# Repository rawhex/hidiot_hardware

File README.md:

# HIDIOT Hardware

This is the repo for the HIDIOT hardware. It contains the following:

* HIDIOT Schematics and Board definitions for Eagle CAD
* HIDIOT Schematic in PNG format
* This README

The HIDIOT uses the Arduino IDE in either Trinket or Digispark compatible configuration with the appropriate software. Digispark is the preferred framework. Please see [here](https://github.com/digistump/DigistumpArduino) for source code, including the V-USB library used for communication.

## Creating your own HIDIOT

There's a couple of gotchas that you should be aware of depending on what you're using it for and what modifications you want to make. It's probably best to drop an email to pcb@hidiot.com where we can help you make sure your design both works properly and respects our trademarks.

If you're looking to make one for your own personal use, please do fill your boots (but let us know above so we can help).

If you want to create HIDIOTs for an event or a group, we're more than happy for you to do so providing you make your board substantially unique in some way, and you obviously can't use the terms HIDIOT or Raw Hex in your designor name without express written permission. If you want to use these terms, just write to us, and we'll have a chat.

If you're looking to create HIDIOTs commercially, then please make sure that your HIDIOT has a fundamental difference, and of course you can't use terms like HIDIOT or Raw Hex anywhere in your product's design or implementation. You'll also need to be careful about how you use our documentation, which is licenced separately. Talking to us up front will help avoid possible problems later on and we're happy to advise on how to do this correctly.

## Partnering with us

We do provide custom board designs and can provide licences and support for various forms of commercial use. Please contact us at support at rawhex dot com. We'd love to work with you!

## Thanks

There are several people we'd like to thank. All of these people helped, possibly without knowing it. Without these people the HIDIOT would not be possible. If you're not on the list and think you should be, drop us a line.

* Sammy Verity
* Dominic Spill
* Erik Kettenburg
* Saumil Shah
* Dhillon 'L33tdawg' Kannabhiran
* Pete Herzog
* Joe Fitzpatrick
* Don A. Bailey
* cpldcpu
* Jenna Fox
* ihsan Kehribar
* Objective Development Software GmBH
* All of our Kickstarter backers

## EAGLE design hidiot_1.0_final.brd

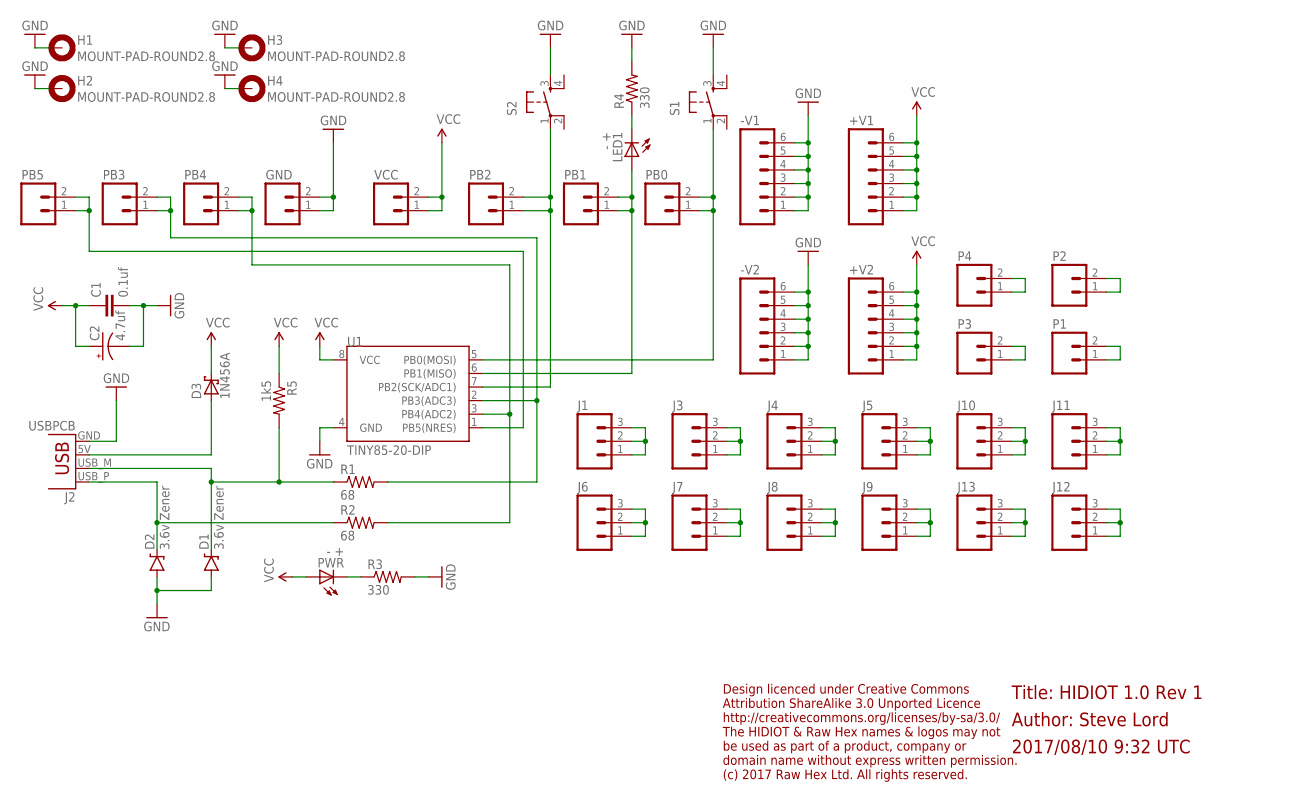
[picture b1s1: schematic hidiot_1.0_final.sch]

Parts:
+V1, +V2: M06SILK_FEMALE_PTH; 1X06
-V1, -V2: M06SILK_FEMALE_PTH; 1X06
C1: 0.1uf; CAP-PTH-SMALL-KIT; MPN K104K15X7RF5TH5
C2: 4.7uf; CPOL-RADIAL-100UF-25V; MPN MCGPR50V475M5X11
D1, D2: 3.6v Zener; DIODE-ZENER; MPN 1N4729A
D3: 1N456A; DIODE_DO35-7; MPN 1N456A
GND: M02PTH; 1X02
H1, H2, H3, H4: MOUNT-PAD-ROUND2.8; 2,8-PAD
J1, J3, J4, J5, J6, J7, J8, J9, J10, J11, J12, J13: M03PTH; 1X03
J2: USBPCB; USB-A-PCB
LED1: - +; LED3MM; MPN HLMP-K150
P1, P2, P3, P4: M02PTH; 1X02
PB0, PB1, PB2, PB3, PB4, PB5: M02PTH; 1X02
PWR: - +; LED3MM; MPN HLMP-K150
R1, R2: 68; AXIAL-0.4; MPN MCF 0.25W 68R
R3, R4: 330; AXIAL-0.4; MPN MCF 0.25W 68R
R5: 1k5; AXIAL-0.4; MPN MCF 1W 1K5
S1, S2: TAC_SWITCHPTH; TACTILE-PTH
U1: TINY85-20-DIP; DIP08; MPN ATTINY85-20PU
VCC: M02PTH; 1X02

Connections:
GND: -V1.1, -V1.2, -V1.3, -V1.4, -V1.5, -V1.6, -V2.1, -V2.2, -V2.3, -V2.4, -V2.5, -V2.6, C1.2, C2.2 (-), D1.P$2 (A), D2.P$2 (A), GND.1, GND.2, H1.B2,8, H2.B2,8, H3.B2,8, H4.B2,8, J2.GND, R3.P$2 (2), R4.P$2 (2), S1.3, S2.3, U1.4 (GND)
unnamed: PB5.1, PB5.2, U1.1 (PB5(NRES))
unnamed: LED1.K (C), R4.P$1 (1)
unnamed: PB2.1, PB2.2, S2.1, U1.7 (PB2(SCK/ADC1))
unnamed: PB3.1, PB3.2, R1.P$2 (2), U1.2 (PB3(ADC3))
unnamed: PB4.1, PB4.2, R2.P$2 (2), U1.3 (PB4(ADC2))
unnamed: PB0.1, PB0.2, S1.1, U1.5 (PB0(MOSI))
unnamed: D2.P$1 (C), J2.USB_P (D+), R2.P$1 (1)
unnamed: D1.P$1 (C), J2.USB_M (D-), R1.P$1 (1), R5.P$2 (2)
unnamed: D3.A (C), J2.5V (VBUS)
unnamed: LED1.A, PB1.1, PB1.2, U1.6 (PB1(MISO))
unnamed: PWR.K (C), R3.P$1 (1)
unnamed: J1.1, J1.2, J1.3
unnamed: J3.1, J3.2, J3.3
unnamed: J4.1, J4.2, J4.3
unnamed: J5.1, J5.2, J5.3
unnamed: J8.1, J8.2, J8.3
unnamed: J7.1, J7.2, J7.3
unnamed: J6.1, J6.2, J6.3
unnamed: J9.1, J9.2, J9.3
unnamed: J10.1, J10.2, J10.3
unnamed: J11.1, J11.2, J11.3
unnamed: J12.1, J12.2, J12.3
unnamed: J13.1, J13.2, J13.3
unnamed: P1.1, P1.2
unnamed: P2.1, P2.2
unnamed: P3.1, P3.2
unnamed: P4.1, P4.2
VCC: +V1.1, +V1.2, +V1.3, +V1.4, +V1.5, +V1.6, +V2.1, +V2.2, +V2.3, +V2.4, +V2.5, +V2.6, C1.1, C2.1 (+), D3.C (A), PWR.A, R5.P$1 (1), U1.8 (VCC), VCC.1, VCC.2

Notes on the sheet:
Author: Steve Lord
Title: HIDIOT 1.0 Rev 1
2017/08/10 9:32 UTC
Design licenced under Creative Commons Attribution ShareAlike 3.0 Unported Licence http://creativecommons.org/licenses/by-sa/3.0/ The HIDIOT & Raw Hex names & logos may not be used as part of a product, company or domain name without express written permission. (c) 2017 Raw Hex Ltd. All rights rese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

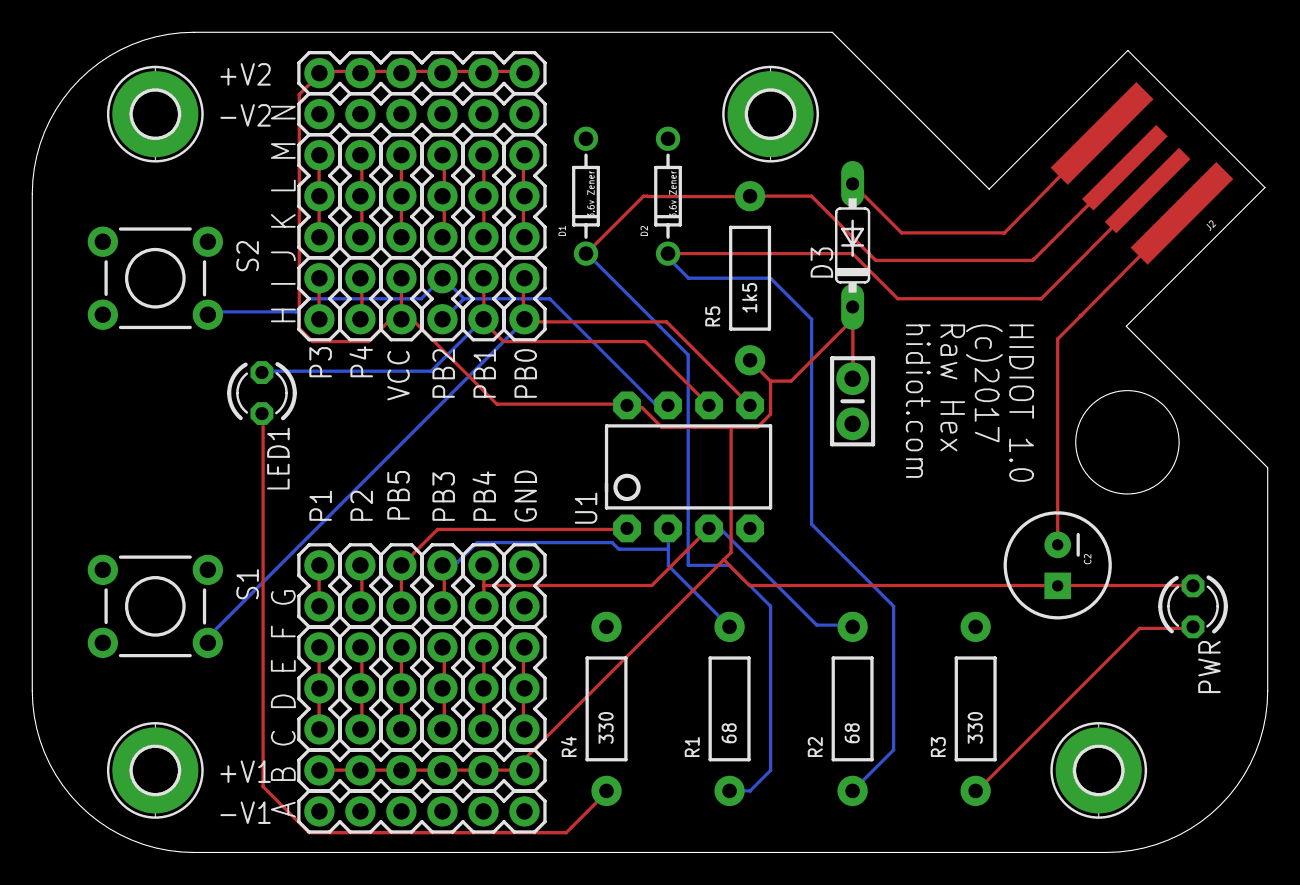
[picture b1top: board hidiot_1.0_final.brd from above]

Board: 2 copper layers, 76.5 x 50.8 mm, 48 parts (0 on the bottom side), 29 nets.

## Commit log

2017-08-10 Initial release of rev1/issue 1 board drawings
2017-08-10 Formatting goof
2017-08-10 Thanks added
2017-08-15 More thanks added

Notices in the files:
hidiot_1.0_final.sch:
(c) 2017 Raw Hex Ltd. All rights reserved.
parts and their libraries:
SparkFun-Passives: Licensing: Creative Commons ShareAlike 4.0 International - https://creativecommons.org/licenses/by-sa/4.0
